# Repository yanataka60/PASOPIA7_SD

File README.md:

# TOSHIBA PASOPIA7、PASOPIAにSD-Cardとのロード、セーブ機能

　TOSHIBA PASOPIA7、PASOPIA(T-BASIC Ver1.1)でCMTの代わりにSD-CARDからロード、セーブを実現するものです。

　SDから読み込めるCMTのファイル形式はEMUで一般的なWAV、CASには対応していません。bugfire2009さんのDumpListEditorを使ってバイナリ形式に変換したものを使います。

　機械語 -> 各モデル固有ヘッダ付きBINファイル、拡張子は.bin

　BASIC -> BASファイル、拡張子は.bas

　CMTからの読み込み実行に数分掛かっていたゲームも数十秒で実行できます。

　ただし、CMT用プログラムのすべてがSD対応となるわけではありません。特に市販ゲームはCMT読み込みに独自ルーチンを使っているものもあるため、SD対応は不明です。

　なお、Arduino、ROMへ書き込むための機器が別途必要となります。

#### 　PASOPIAは、T-BASIC Ver1.1のみの対応です。また、OA-BASICも未対応です。

## 重要!!
　PASOPIA、PASOPIA7においてあるあるの電源ユニット部フィルムコンデンサの破裂ですが、修理に適切な品への交換されていない場合、電源電圧は正常(+5V)なのに信号電圧が異常(+10V程度)な状態となることがあるようです。

　私は当初電源電圧が正常であることを確認したものの原因が判らずArduino及びUSBシリアル変換モジュールを数個破壊してしまいました。

　当方ではCZRD信号の電圧が異常だったため、念のためPASOPIA7_SD基板にCZRD信号電圧を測るための「J6 TEST_VOL」端子を設けてあります。

　ICを装着する前に電圧をチェックし、+5V以上の電圧が出ているようであればまず電源ユニット部フィルムコンデンサを適切な品に交換してください。

　また、事前に調査するのであればPAC SLOT2 15Pin(CRD)の電圧を測ってみてください。

## 回路図(PASOPIA7、PASOPIA共通)
　PASOPIA7_SD本体基板とPASOPIA7_SD_ROM基板に分かれています。

　SDアクセスルーチンを読み込むためにPASOPIA7_SD_ROM基板(読込専用RAMPAC)を使用します。

　XPAC2又はRAMPACを持っていればそれにCMTから読み込んだSDアクセスルーチンを保存しておくことで使用することも可能です。詳細は後述の「XPAC2又はRAMPACの使用」を参照してください。

### PASOPIA7_SD本体基板
　KiCadフォルダ内のPASOPIA7_SD.PDFを参照してください。

[回路図](https://github.com/yanataka60/PASOPIA7_SD/blob/main/Kicad/1.6/PASOPIA7_SD.pdf)

## 部品
|番号|品名|数量|備考|
| ------------ | ------------ | ------------ | ------------ |
|J1|2x25ボックスヘッダ|1|共立エレショップ JS-1200R-50など、秋月電子通商 PH-2x40RGなどのピンヘッダでも代用可(注4)|
||J2,J3のいずれか|||
|J2|Micro_SD_Card_Kit|1|秋月電子通商 AE-microSD-LLCNV (注1)|
|J3|MicroSD Card Adapter|1|Arduino等に使われる5V電源に対応したもの(注2)|
|U1|74LS04|1||
|U2|74LS30|1||
|U3|8255|1||
|U4|Arduino_Pro_Mini_5V|1|Atmega328版を使用 168版は不可。(注3)|
|C1-C3|積層セラミックコンデンサ 0.1uF|3||
|C4|電解コンデンサ 16v100uF|1||
|S1|3Pスライドスイッチ|1|秋月電子通商 SS12D01G4など|
|J4|コネクタ 2Pin|1|ピンヘッダで代用するときはGNDと間違えないよう1Pinで5Vだけにしたほうが良い|
|J5|DCジャック|1|秋月電子通商 MJ-179PHなど|
|J6|2P ピンヘッダ|1|秋月電子通商 PH-1x40SGなど|
||2.54mmピッチ2x25Pinフラットケーブル|1||
||PASOPIA7_SDとPASOPIA7_SD_ROMを繋ぐケーブル|15cm～30cm|ジャンプワイヤー メス-メスなど|

PASOPIA7_SDに外部から電源を供給する場合
|番号|品名|数量|備考|
| ------------ | ------------ | ------------ | ------------ |
||ACアダプター 5V|1|秋月電子通商 M050200-A010JPなど|

### 注1)秋月電子通商　AE-microSD-LLCNVのJ1ジャンパはショートしてください。

### 注2)MicroSD Card Adapterを使う場合

J3に取り付けます。

MicroSD Card Adapterについているピンヘッダを除去してハンダ付けするのが一番確実ですが、J2の穴にMicroSD Card Adapterをぴったりと押しつけ、裏から多めにハンダを流し込むことでハンダ付けをする方法もあります。なお、この方法の時にはしっかりハンダ付けが出来たかテスターで導通を確認しておいた方が安心です。

ハンダ付けに自信のない方はJ1の秋月電子通商　AE-microSD-LLCNVをお使いください。AE-microSD-LLCNVならパワーLED、アクセスLEDが付いています。

### 注3)Arduino Pro MiniはA4、A5ピンも使っています。

#### 注4)ピンヘッダで代用するときは、基板から若干浮かせてピンヘッダをハンダ付けするとフラットケーブルをスムーズに抜き差しできます。

### PASOPIA7_SD_ROM基板
　KiCadフォルダ内のPASOPIA7_SD.PDFを参照してください。

[回路図](https://github.com/yanataka60/PASOPIA7_SD/blob/main/Kicad/ROM/PASOPIA7_SD_ROM.pdf)

|番号|品名|数量|備考|
| ------------ | ------------ | ------------ | ------------ |
|U1|74LS04|1||
|U2|74LS00|1||
|U3|74LS20|1||
|U4-U5|74LS273|2||
|U6|ROM 27256/29C256又は27512/27C512相当品|1|入手しやすいものでOK、28C256は不可|
|U7|74LS245|1||
|C1-C7|積層セラミックコンデンサ 0.1uF|7||
|C8|電解コンデンサ 16v100uF|1||
|S1|3Pin ピンヘッダーとジャンパーピン又は3Pスライドスイッチ|1|秋月電子通商 SS12D01G4など|
|J2|コネクタ 2Pin|1|ピンヘッダで代用するときはGNDと間違えないよう1Pinで5Vだけにしたほうが良い|

## 取り付け(PASOPIA7、PASOPIA共通)
　PASOPIA7_SD本体基板はPASOPIA7(PASOPIA)本体後部の拡張端子とフラットケーブルで接続します。50Pinフラットケーブルは、コネクタのボッチとケーブルの返しが両方上になる側のコネクタを本体に嵌めます。

　ケーブルの返しを下にして本体に嵌めると一見嵌っているように見えても接触不良を起こしていることがあります。

.JPG)

　PASOPIA7_SD_ROM基板はPACスロット2に挿入します。この時PASOPIA7_SD_ROM基板は部品実装面を手前にして挿入してください。基板の右端をスロットの右に合わせるように挿入すればズレずに挿入できると思います。

　次にPASOPIA7_SD_ROM基板への+5V供給のため、PASOPIA7_SD_ROM基板の+5V端子(J2)とPASOPIA7_SD本体基板の+5V端子(J4)を繋いでください。

.JPG)

　XPAC2又はRAMPACを使用するときは、外部電源として5V電源アダプタを接続するか、内部電源としてPAC SLOT1の43Pin又は44Pinから+5Vを取り出してジャンプワイヤー オス-メスなどで接続します。

## ROMへの書込み(PASOPIA7、PASOPIA共通)
　Z80フォルダ内のRAMPAC.binをROMライター(TL866II Plus等)を使って27256又は27512に書き込みます。

　実際に使用しているのは32KByte分(32Kx8)です。

　PASOPIA7_SD_ROM基板のROMはPASOPIA7(PASOPIA)からはRAMPACとして扱われます。(PASOPIA7(PASOPIA)から書き込みはできません。)

## RAMPAC.binに登録されているファイル
　RAMPAC.binに登録されているファイルは次の2つになります。

|ファイル名|種類|備考|
| ------------ | ------------ | ------------ |
|sd|BASIC|PASOPIA7用|
|SDBOOT|BINARY|PASOPIA7用|
|sdt|BASIC|PASOPIA用|
|SDTBOOT|BINARY|PASOPIA用|

　また、RAMPAC.binへのファイル登録はTAKEDAさんのEMU ePASOPIA7で行っており、RAMPAC1としてファイルを選択すればePASOPIA7から読み書き出来ます。

## XPAC2又はRAMPACの使用(PASOPIA7、PASOPIA共通)
　XPAC2又はRAMPACを持っていればPASOPIA7_SD_ROM基板の代わりに使用できます。

　ただし、PASOPIA7_SD本体基板への+5V供給を独自に用意する必要があります。内部から引き出すか、5V電源アダプタを用意するかですが、PACスロット1 44Pinから取るのが簡単だと思います。

### XPAC2
　ePASOPIA7で扱うRAMPACKが32KByteなのに対してXPAC2で扱うSLOT4は64KByteです。

　XPAC2のSD-CARDへRAMPAC.binをコピーしてXPAC2 SLOT4へ登録することも可能とは思われますが、容量が32KByteとなってしまう気がします。

　XPAC2 SLOT4を64KByteのまま使いたいのであればsd.wav(sdt.wav)、SDBOOT.wav(SDTBOOT.wav)をCMTインタフェースから読み込み、XPAC2 SLOT4へ保存してください。

### RAMPAC
　RAMPAC.binをRAMPACへ登録する方法がありませんのでsd.wav(sdt.wav)、SDBOOT.wav(SDTBOOT.wav)をCMTインタフェースから読み込み、RAMPACへ保存してください。

## Arduinoプログラム(PASOPIA7、PASOPIA共通)
　Arduino IDEを使ってArduinoフォルダのPASOPIA7_SDフォルダ内PASOPIA7_SD.inoを書き込みます。

　SdFatライブラリを使用しているのでArduino IDEメニューのライブラリの管理からライブラリマネージャを立ち上げて「SdFat」をインストールしてください。

　「SdFat」で検索すれば見つかります。「SdFat」と「SdFat - Adafruit Fork」が見つかりますが「SdFat」のほうを使っています。

注)Arduinoを基板に直付けしている場合、Arduinoプログラムを書き込むときは、PASOPIA7(PASOPIA)本体とは接続を外し、U1 74LS04を外したうえで書き込んでください。

## SD-CARD(PASOPIA7、PASOPIA共通)
　出来れば8GB以下のSDカードを用意してください。

　ArduinoのSdFatライブラリは、SD規格(最大2GB)、SDHC規格(2GB～32GB)に対応していますが、SDXC規格(32GB～2TB)には対応していません。

　また、SDHC規格のSDカードであっても32GB、16GBは相性により動作しないものがあるようです。

　FAT16又はFAT32が認識できます。NTFSは認識できません。

## 操作方法
### PASOPIA7
　起動直後に「RUN"sd"」を実行してSDアクセスルーチンの読込、初期化の実行を行います。

　SDアクセスルーチンはE800h～EFCFhに読み込まれます。

　SDアクセスメニューを表示するにはA=&HE800:CALL Aを実行しますが、PF6ファンクションキーに登録してありますのでPF6ファンクションキーを押しても大丈夫です。

### PASOPIA(T-BASIC Ver1.1のみ対応)
　起動直後に「RUN"sdt"」を実行してSDアクセスルーチンの読込、初期化の実行を行います。

　SDアクセスルーチンはF000h～F776hに読み込まれます。

　SDアクセスメニューを表示するにはA=&HF000:CALL Aを実行しますが、PF6ファンクションキーに登録してありますのでPF6ファンクションキーを押しても大丈夫です。

#### 扱えるファイル(PASOPIA7、PASOPIA共通)
bugfire2009さんのDumpListEditorを使ってバイナリ形式に変換したものを使います。

扱う機種をPASOPIA7に変更したうえで変換します。

##### 機械語 -> 「BINファイル書出し(各モデル固有ヘッダ付き)」で保存、拡張子は.bin

##### BASIC -> 「BASファイル書出し」で保存、拡張子は.bas

### コマンド(PASOPIA7、PASOPIA共通)
　コマンド入力時にBSキー又は左カーソルキーで直前に入力した文字を訂正できます。

　CLR、HOME、上・下・右カーソルキーは画面が乱れるだけで入力文字の訂正は出来ません。

#### SD[RETURN]又はSD 文字列[RETURN]
　文字列を入力せずにSD[RETURN]のみ入力するとSD-CARDルートディレクトリにあるファイルの一覧を表示します。

　文字列を付けて入力すればSD-CARDルートディレクトリにあるその文字列から始まるファイルの一覧を表示します。
　10件表示したところで指示待ちになるのでESCキーで終了、Bキー又はBSキーで前の10件に戻ります。それ以外のキーで次の10件を表示します。

　表示される順番は、登録順となりファイル名アルファベッド順などのソートした順で表示することはできません。

　LOADしたいファイルを見つけたら左端の数字のキーを押せばLOADされます。

　BASICプログラムか、機械語プログラムかは自動で判断します。

　なお、PASOPIA7はE7FFh以降、PASOPIAはEFFFH以降へ機械語プログラムがLOADされた場合、次の五段階の挙動となります。

||PASOPIA7|PASOPIA|挙動|
|---- | ------------ | ------------ | ------------ |
|1|～E8FCh|～F0FAh|機械語プログラムをLOAD後は、SM,SBコマンドが使用できなくなります。LM,LG,LB,SD,J,Q,Bコマンドは使用できます。|
|2|～EC54h|～F423h|機械語プログラムをLOAD後は、J,Q,Bのみ使えます。SD,LMコマンドでLOADした後、Jコマンドでの実行は可能です。|
|3|～EDC6h|～F582h|BASICプログラムLOADの限界です。通常はCLEAR文で設定したメインメモリの上限E800hですが、F000hに変更すればEDC6hまでのBASICプログラムを一度だけLOAD出来ます。|
|4|～EE61h|～F614h|BASIC中からはこれ以降への機械語LOADは出来ません。|
|5|～EEE7h|～F691h|機械語プログラムをLOAD後は、すべてのコマンドが使えません。EDC7h以降までLOADされた場合は強制的に実行番地にジャンプを試みます。|

##### 例)
　　SD[RETURN]

　　SD S[RETURN]

　　SD SP[RETURN]

#### LM DOSファイル名[RETURN]
　指定したDOSフィル名の機械語プログラムをSD-CARDからLOADします。

　拡張子が「bin」であるファイルだけが対象でファイル名の最後が「.BIN」でない場合には自動的に付加されます。

　なお、PASOPIA7はE7FFh以降、PASOPIAはEFFFH以降へ機械語プログラムがLOADされた場合、次の五段階の挙動となります。

||PASOPIA7|PASOPIA|挙動|
|---- | ------------ | ------------ | ------------ |
|1|～E8FCh|～F0FAh|機械語プログラムをLOAD後は、SM,SBコマンドが使用できなくなります。LM,LG,LB,SD,J,Q,Bコマンドは使用できます。|
|2|～EC54h|～F423h|機械語プログラムをLOAD後は、J,Q,Bのみ使えます。SD,LMコマンドでLOADした後、Jコマンドでの実行は可能です。|
|3|～EDC6h|～F582h|BASICプログラムLOADの限界です。通常はCLEAR文で設定したメインメモリの上限E800hですが、F000hに変更すればEDC6hまでのBASICプログラムを一度だけLOAD出来ます。|
|4|～EE61h|～F614h|BASIC中からはこれ以降への機械語LOADは出来ません。|
|5|～EEE7h|～F691h|機械語プログラムをLOAD後は、すべてのコマンドが使えません。EDC7h以降までLOADされた場合は強制的に実行番地にジャンプを試みます。|

##### 例)
　　LM TEST[RETURN] -> DOSファイル名「TEST.BIN」を読み込みます。

　　LM TEST.BIN[RETURN] -> DOSファイル名「TEST.BIN」を読み込みます。

　　LM TEST.BAS[RETURN] -> DOSファイル名「TEST.BAS.BIN」を読み込みます。

#### LG DOSファイル名[RETURN]
　指定したDOSフィル名の機械語プログラムをSD-CARDからLOADした後、実行開始アドレスへジャンプします。

　LOAD後そのまま実行するのでFF64hまでLOADしても大丈夫です。

　LOADした後、実行開始アドレスへジャンプする以外はLMコマンドと同じです。

#### LB DOSファイル名[RETURN]
　現在選択しているPROGエリアに指定したDOSフィル名のBASICプログラムをSD-CARDからLOADします。

　LOADするPROGエリアを切り替えたい場合にはSDメニューに入る前に切り替えておいてください。

　拡張子が「BAS」であるファイルだけが対象でファイル名の最後が「.BAS」でない場合には自動的に付加されます。

##### 例)
　　LB TEST[RETURN] -> DOSファイル名「TEST.BAS」を読み込みます。

　　LB TEST.BAS[RETURN] -> DOSファイル名「TEST.BAS」を読み込みます。

　　LB TEST.BIN[RETURN] -> DOSファイル名「TEST.BIN.BAS」を読み込みます。

#### SM XXXX,YYYY,DOSファイル名[RETURN]　(XXXX,YYYYは16進数4桁を表す文字列)
　XXXX番地からYYYY番地までの機械語プログラムを指定したDOSフィル名でSD-CARDにSAVEします。

　拡張子の指定「.BIN」は省略することが出来、ファイル名の最後が「.BIN」でない場合には自動的に付加されます。

##### 例)
　　SM B000,BFFF,TEST[RETURN] -> B000h～BFFFhまでをDOSファイル名「TEST.BIN」でSAVEします。

　　SM B000,BFFF,TEST.BIN[RETURN] -> B000h～BFFFhまでをDOSファイル名「TEST.BIN」でSAVEします。

　　SM B000,BFFF,TEST.BAS[RETURN] -> B000h～BFFFhまでをDOSファイル名「TEST.BAS.BIN」でSAVEします。

#### SB DOSファイル名[RETURN]
　現在選択しているPROGエリアのBASICプログラムを指定したDOSフィル名でSD-CARDにSAVEします。

　SAVEするPROGエリアを切り替えたい場合にはSDメニューに入る前に切り替えておいてください。

　拡張子の指定「.BAS」は省略することが出来、ファイル名の最後が「.BAS」でない場合には自動的に付加されます。

##### 例)
　　SB TEST[RETURN] -> DOSファイル名「TEST.BAS」でSAVEします。

　　SB TEST.BAS[RETURN] -> DOSファイル名「TEST.BAS」でSAVEします。

　　SB TEST.BIN[RETURN] -> DOSファイル名「TEST.BIN.BAS」でSAVEします。

#### J[RETURN]又はJ 16進数4桁[RETURN]
　Jだけの場合は、直前にLOADした機械語プログラムの先頭番地へジャンプします。

　16進数4桁を指定した場合は16進数4桁が表すアドレスにジャンプします。

　Jの後ろに空白があっても無くても構いません。

#### B[RETURN]又はQ[RETURN]
　BASICに復帰します。

### BASICプログラム中から機械語プログラムをLOADする
#### PASOPIA7
　BASICプログラム中に「CALL &HE803:REM ファイル名」と記述することで機械語プログラムをLOAD出来ます。

　ファイル名はSDカードに保存されている拡張子も含めたファイル名を記述します。

　通常LOAD可能なのはCLEAR文で設定したメインメモリの上限E7FFhですが、F000hに変更すればEE61hまでのBASICプログラムをLOAD出来ます。

##### 例)

20 B=&HE803:CALL B:REM antiair.bin

#### PASOPIA(T-BASIC Ver1.1)
　BASICプログラム中に「CALL &HF003:REM ファイル名」と記述することで機械語プログラムをLOAD出来ます。

　ファイル名はSDカードに保存されている拡張子も含めたファイル名を記述します。

　通常LOAD可能なのはCLEAR文で設定したメインメモリの上限EFFFhですが、F7FChに変更すればF614hまでのBASICプログラムをLOAD出来ます。

##### 例)

20 B=&HE803:CALL B:REM antiair.bin

## 未解決事項(2025.8.11)
　PASOPIA7_SDからPASOPIA、PASOPIA7の両機種でいぬふと様のゲームを起動したとき、以下の症状が出ることがあります。

#### 　原因を調査中ですが特定に至っていません。しかし、CMTからの起動においては症状はでませんのでいぬふと様のゲームに問題があるのではなく、PASOPIA7_SD側の問題と思われますのでこの件に関していぬふと様に問い合わせることはご遠慮くださるようお願いします。

### PASOPIA
　表示がずれます。ゲーム起動直前にwidth 40を実行すると回避できるようです。

　PASOPIA7_SD起動時にwidth 40:width 36としていますが、それでも表示がずれる場合にはゲーム起動直前にwidth 40を実行してから起動してみてください。

### PASOPIA7
　いくつかのゲームで何も押していないのに勝手にキー入力され続けてしまうことがあります。また症状が出るときと出ない時があり、原因の特定に至っていません。

　症状が出ない時には普通にゲームができます。今のところ、回避方法、対策が見つかっていません。

## 操作上の注意
　電源を入れたままSD-CARDの抜き差しをする場合又は「SD-CARD INITIALIZE ERROR」と表示されたときは、SD-CARDを挿入後、SD、LM、LBコマンド等でSD-CARDに3回ほどアクセスすれば復旧します。

　SD-CARDの抜き差しは電源を切った状態で行うほうがより確実です。

## 謝辞
　基板の作成に当たり以下のデータを使わせていただきました。ありがとうございました。

　Arduino Pro Mini

　　https://github.com/g200kg/kicad-lib-arduino

　AE-microSD-LLCNV

　　https://github.com/kuninet/PC-8001-SD-8kRAM

## 追記
2025.8.14 PASOPIAはT-BASIC Ver1.1のみ対応していることを追記。BASICプログラム中から機械語プログラムをLOADするときのファイル名には拡張子も含めることを追記。

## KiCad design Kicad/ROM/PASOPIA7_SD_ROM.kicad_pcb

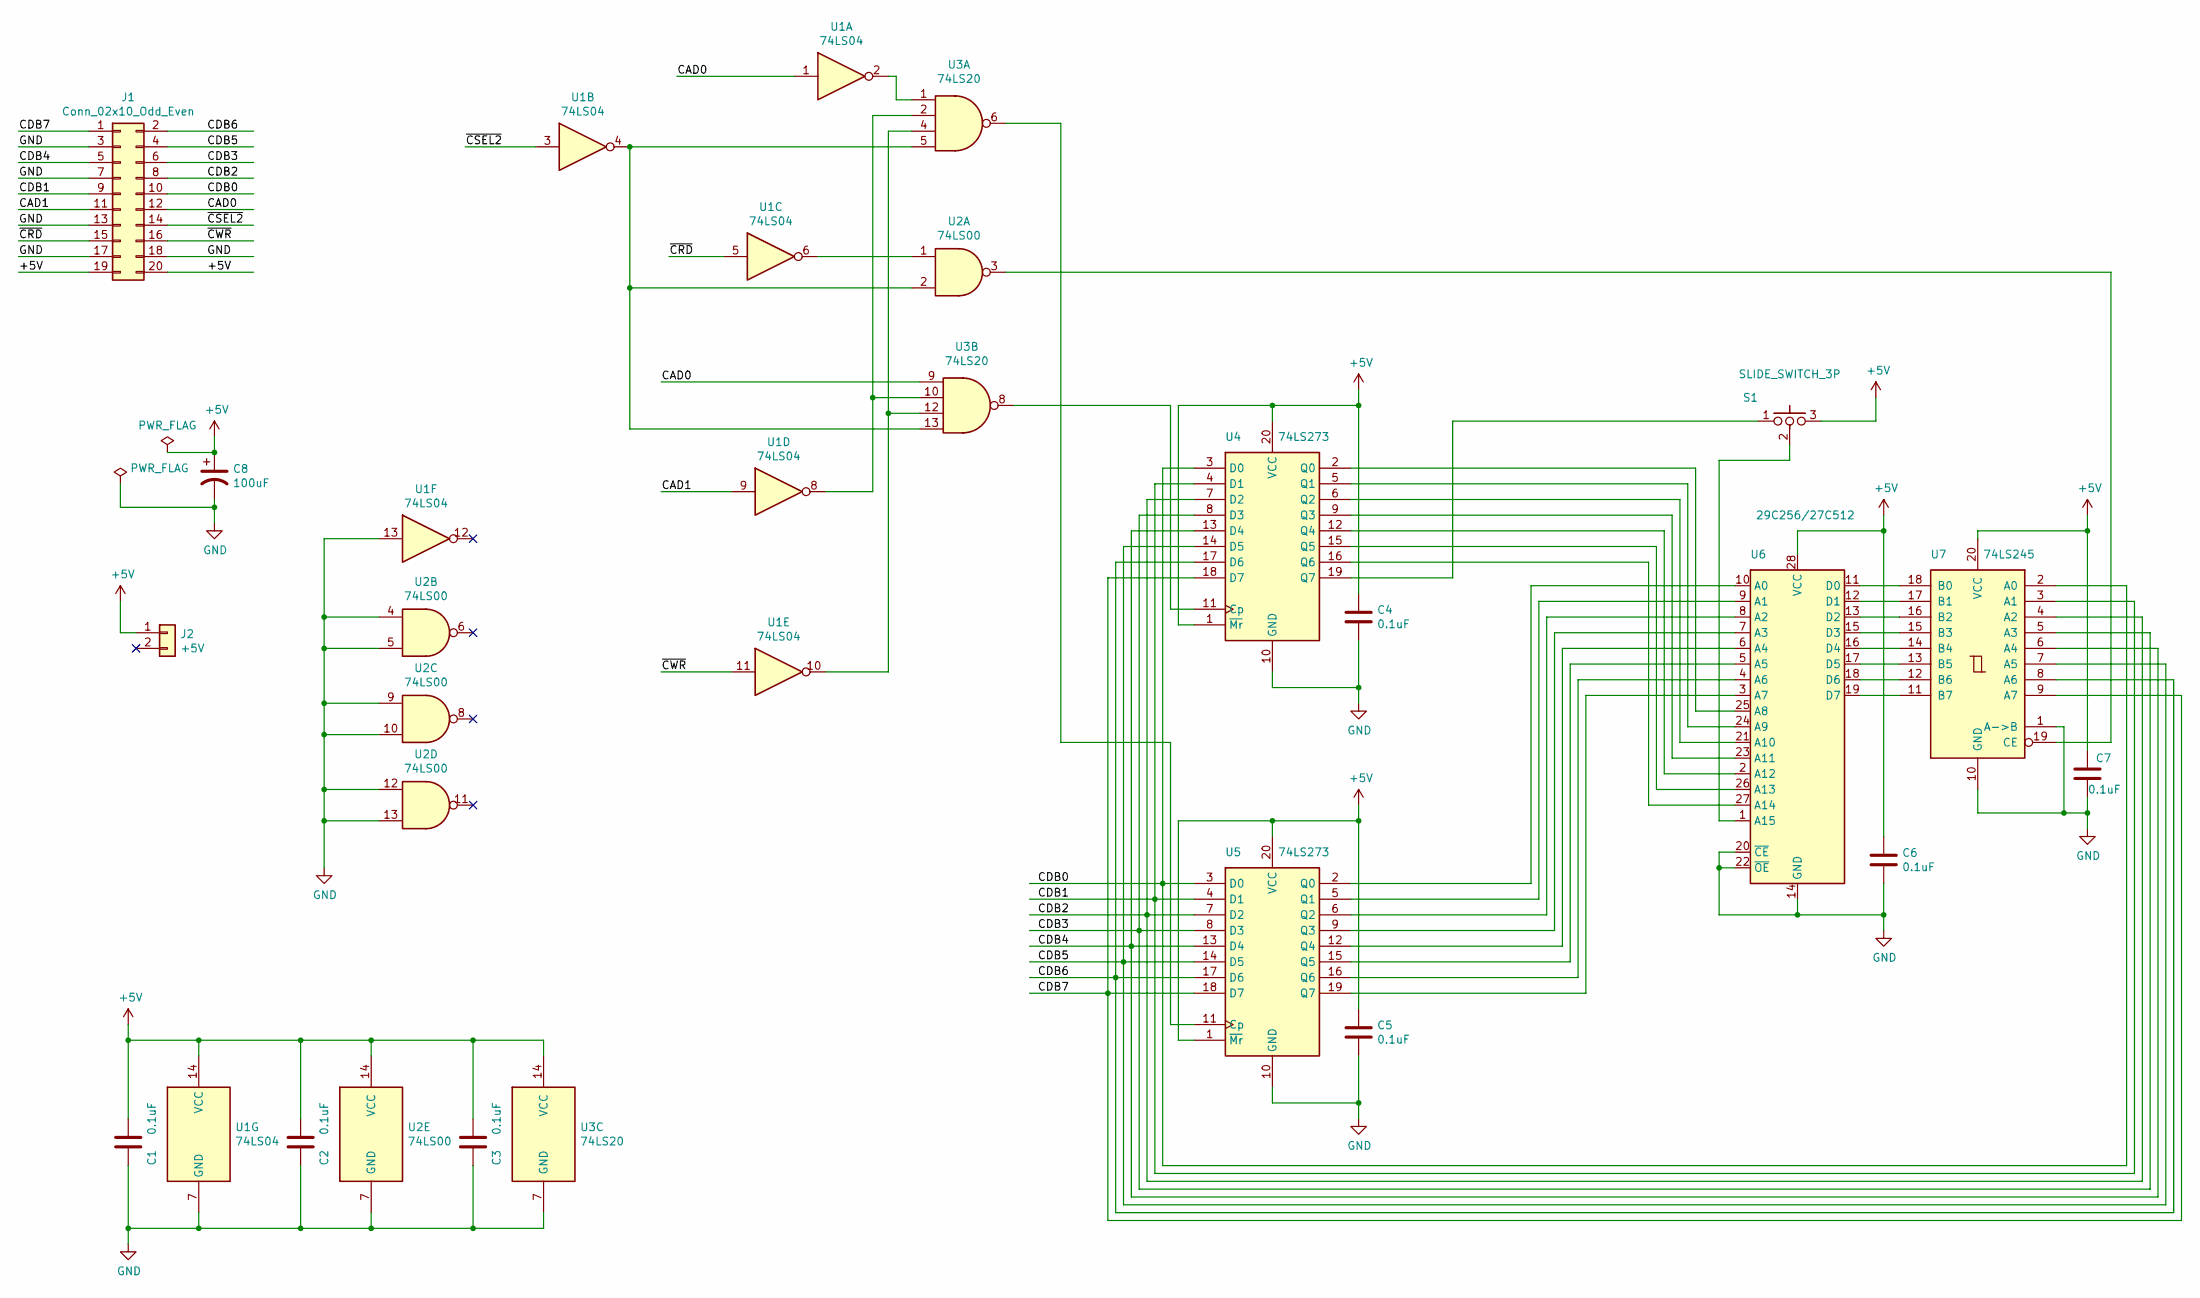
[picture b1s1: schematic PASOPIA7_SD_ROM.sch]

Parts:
C1, C2, C3, C4, C5, C6, C7: 0.1uF; C_Rect_L4.0mm_W2.5mm_P2.50mm
C8: 100uF; CP_Radial_D5.0mm_P2.50mm
J1: Conn_02x10_Odd_Even; PinHeader_2x10_P2.54mm_Vertical
J2: +5V; PinHeader_1x02_P2.54mm_Horizontal
S1: SLIDE_SWITCH_3P; PinHeader_1x03_P2.54mm_Vertical
U1: 74LS04; DIP-14_W7.62mm_LongPads
U2: 74LS00; DIP-14_W7.62mm_LongPads
U3: 74LS20; DIP-14_W7.62mm_LongPads
U4, U5: 74LS273; DIP-20_W7.62mm_LongPads
U6: 29C256/27C512; DIP-28_W15.24mm_LongPads
U7: 74LS245; DIP-20_W7.62mm_LongPads

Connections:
+5V: C1.2, C2.2, C3.2, C4.1, C5.1, C6.1, C7.1, C8.1, J1.19, J1.20, J2.1, S1.3, U1.14 (VCC), U2.14 (VCC), U3.14 (VCC), U4.1 (~Mr), U4.20 (VCC), U5.1 (~Mr), U5.20 (VCC), U6.28 (VCC), U7.20 (VCC)
/CAD0: J1.12, U1.1, U3.9
/CAD1: J1.11, U1.9
/CDB0: J1.10, U4.3 (D0), U5.3 (D0), U7.2 (A0)
/CDB1: J1.9, U4.4 (D1), U5.4 (D1), U7.3 (A1)
/CDB2: J1.8, U4.7 (D2), U5.7 (D2), U7.4 (A2)
/CDB3: J1.6, U4.8 (D3), U5.8 (D3), U7.5 (A3)
/CDB4: J1.5, U4.13 (D4), U5.13 (D4), U7.6 (A4)
/CDB5: J1.4, U4.14 (D5), U5.14 (D5), U7.7 (A5)
/CDB6: J1.2, U4.17 (D6), U5.17 (D6), U7.8 (A6)
/CDB7: J1.1, U4.18 (D7), U5.18 (D7), U7.9 (A7)
/~CRD: J1.15, U1.5
/~CSEL2: J1.14, U1.3
/~CWR: J1.16, U1.11
GND: C1.1, C2.1, C3.1, C4.2, C5.2, C6.2, C7.2, C8.2, J1.3, J1.7, J1.13, J1.17, J1.18, U1.7 (GND), U1.13, U2.4, U2.5, U2.7 (GND), U2.9, U2.10, U2.12, U2.13, U3.7 (GND), U4.10 (GND), U5.10 (GND), U6.14 (GND), U6.20 (~CE), U6.22 (~OE), U7.1 (A->B), U7.10 (GND)
unnamed: S1.1, U4.19 (Q7)
unnamed: S1.2, U6.1 (A15)
unnamed: U1.2, U3.1
unnamed: U1.4, U2.2, U3.5, U3.13
unnamed: U1.6, U2.1
unnamed: U1.8, U3.2, U3.10
unnamed: U1.10, U3.4, U3.12
unnamed: U2.3, U7.19 (CE)
unnamed: U3.6, U5.11 (Cp)
unnamed: U3.8, U4.11 (Cp)
unnamed: U4.2 (Q0), U6.25 (A8)
unnamed: U4.5 (Q1), U6.24 (A9)
unnamed: U4.6 (Q2), U6.21 (A10)
unnamed: U4.9 (Q3), U6.23 (A11)
unnamed: U4.12 (Q4), U6.2 (A12)
unnamed: U4.15 (Q5), U6.26 (A13)
unnamed: U4.16 (Q6), U6.27 (A14)
unnamed: U5.2 (Q0), U6.10 (A0)
unnamed: U5.5 (Q1), U6.9 (A1)
unnamed: U5.6 (Q2), U6.8 (A2)
unnamed: U5.9 (Q3), U6.7 (A3)
unnamed: U5.12 (Q4), U6.6 (A4)
unnamed: U5.15 (Q5), U6.5 (A5)
unnamed: U5.16 (Q6), U6.4 (A6)
unnamed: U5.19 (Q7), U6.3 (A7)
unnamed: U6.11 (D0), U7.18 (B0)
unnamed: U6.12 (D1), U7.17 (B1)
unnamed: U6.13 (D2), U7.16 (B2)
unnamed: U6.15 (D3), U7.15 (B3)
unnamed: U6.16 (D4), U7.14 (B4)
unnamed: U6.17 (D5), U7.13 (B5)
unnamed: U6.18 (D6), U7.12 (B6)
unnamed: U6.19 (D7), U7.11 (B7)

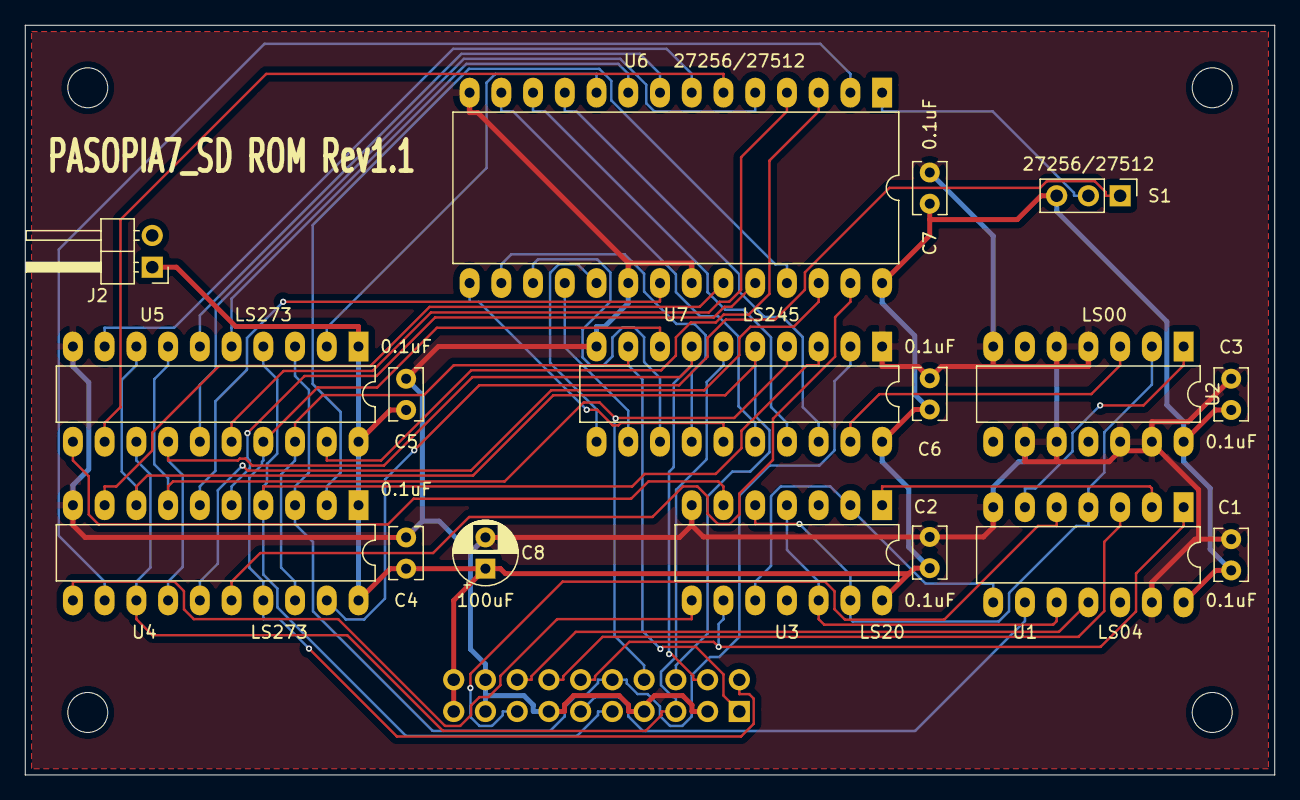
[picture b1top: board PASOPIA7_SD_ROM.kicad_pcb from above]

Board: 2 copper layers, 100.0 x 60.0 mm, 22 parts (1 on the bottom side), 48 nets.

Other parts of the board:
MH1, MH2, MH3, MH4: MountingHole_3.2mm_M3

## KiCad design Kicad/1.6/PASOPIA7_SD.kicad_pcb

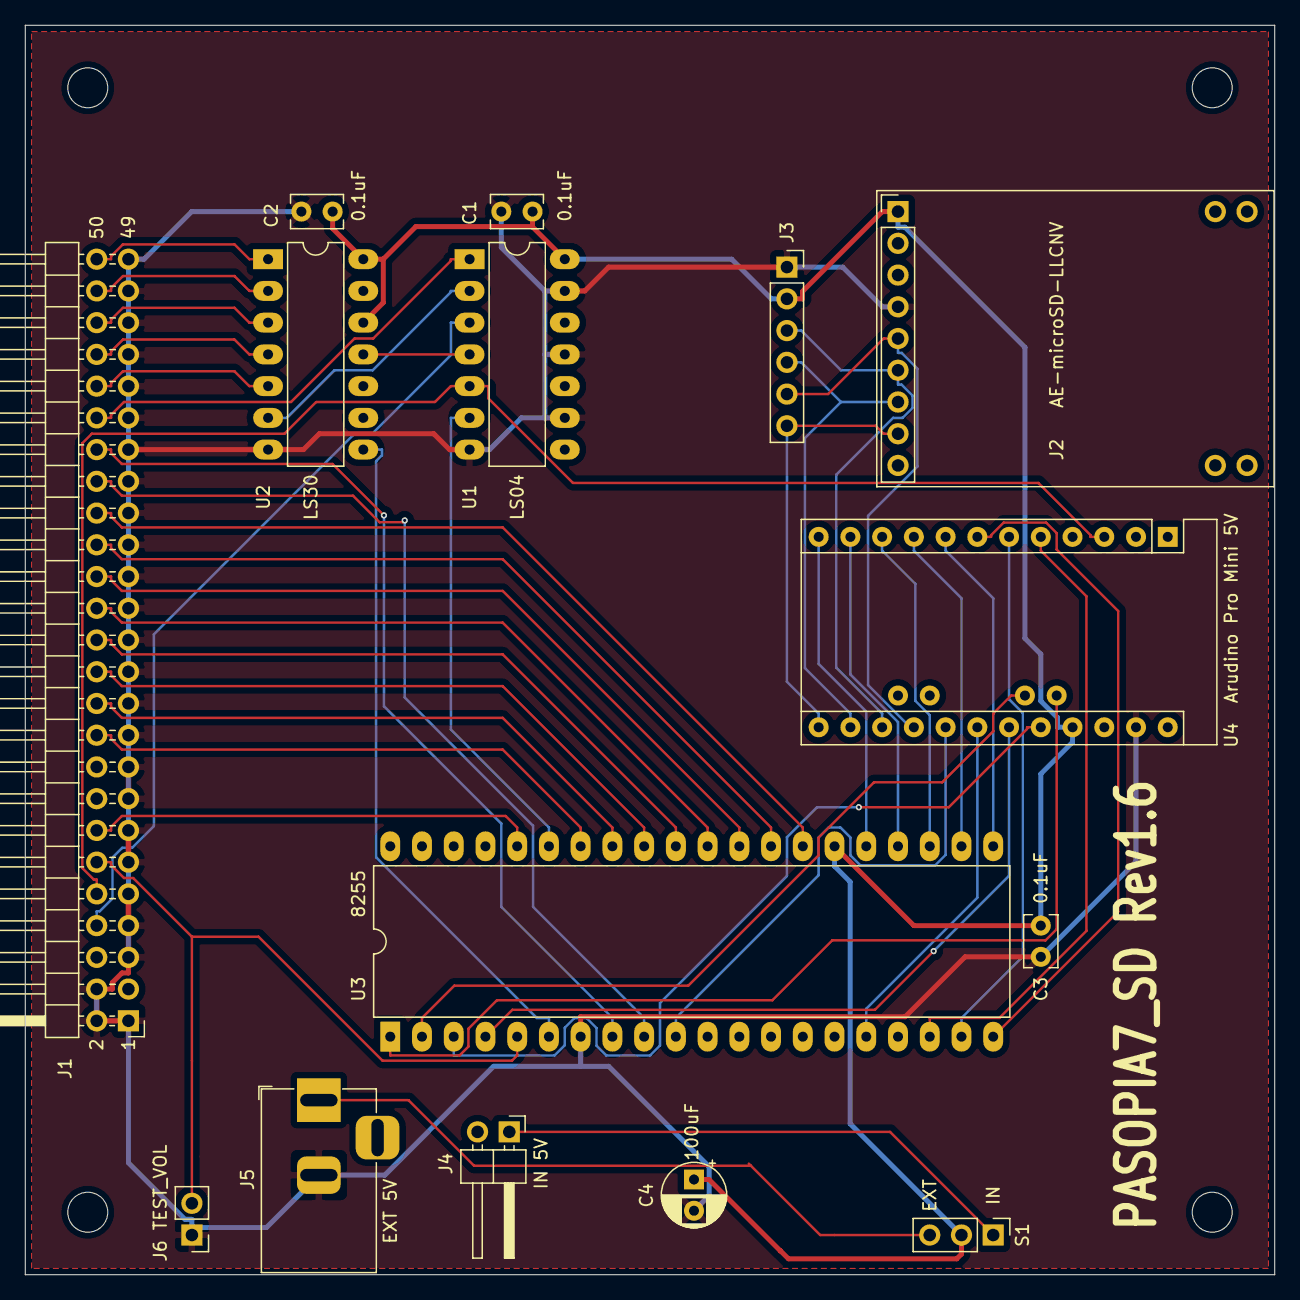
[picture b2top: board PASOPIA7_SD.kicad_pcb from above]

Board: 2 copper layers, 100.0 x 100.0 mm, 19 parts (0 on the bottom side), 46 nets.

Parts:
C1, C2, C3: 0.1uF; C_Rect_L4.0mm_W2.5mm_P2.50mm
C4: 100uF; CP_Radial_D5.0mm_P2.50mm
J1: PASOPIA7 BUS; PinHeader_2x25_P2.54mm_Horizontal
J2: Micro_SD_Card_Kit; AE-microSD-LLCNV
J3: MicroSD Card Adapter; PinSocket_1x06_P2.54mm_Vertical
J4: IN 5V; PinHeader_1x02_P2.54mm_Horizontal
J5: EXT 5V; BarrelJack_Horizontal
J6: TEST_VOL; PinHeader_1x02_P2.54mm_Vertical
MH1, MH2, MH3, MH4: MountingHole_3.2mm_M3
S1: IN / OUT; PinHeader_1x03_P2.54mm_Vertical
U1: 74LS04; DIP-14_W7.62mm_LongPads
U2: 74LS30; DIP-14_W7.62mm_LongPads
U3: 8255; DIP-40_W15.24mm_LongPads
U4: Arduino_Pro_Mini_5V; Arduino_Pro_Mini

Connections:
+5V: C1.2, C2.2, C3.1, C4.1, J2.1, J3.2, S1.2, U1.14, U2.12, U2.14, U3.26, U4.21
/CS: J2.8, J3.6, U4.13
/CZAD0: J1.36, U3.9
/CZAD1: J1.38, U3.8
/CZAD2: J1.40, U1.1
/CZAD3: J1.42, U2.5
/CZAD4: J1.44, U2.4
/CZAD5: J1.46, U2.3
/CZAD6: J1.48, U2.2
/CZAD7: J1.50, U2.1
/CZDB0: J1.20, U3.34
/CZDB1: J1.22, U3.33
/CZDB2: J1.24, U3.32
/CZDB3: J1.26, U3.31
/CZDB4: J1.28, U3.30
/CZDB5: J1.30, U3.29
/CZDB6: J1.32, U3.28
/CZDB7: J1.34, U3.27
/CZIORQ: J1.8, U1.3
/CZRD: J1.12, J6.2, U3.5
/CZRST: J1.10, U1.5, U4.3
/CZWR: J1.14, U3.36
/MISO: J2.6, J3.3, U4.15
/MOSI: J2.7, J3.4, U4.14
/SCK: J2.5, J3.5, U4.16
GND: C1.1, C2.1, C3.2, C4.2, J1.1, J1.2, J1.4, J1.5, J1.7, J1.9, J1.11, J1.13, J1.15, J1.17, J1.19, J1.21, J1.23, J1.25, J1.27, J1.29, J1.31, J1.33, J1.35, J1.37, J1.39, J1.41, J1.43, J1.45, J1.47, J1.49, J2.4, J3.1, J5.2, J6.1, U1.7, U1.9, U1.11, U1.13, U2.7, U3.7, U4.23
unnamed: J4.1, S1.1
unnamed: J5.1, S1.3
unnamed: U1.2, U2.6
unnamed: U1.4, U2.11
unnamed: U1.6, U3.35
unnamed: U2.8, U3.6
unnamed: U3.1, U4.A5
unnamed: U3.2, U4.A4
unnamed: U3.3, U4.20
unnamed: U3.4, U4.19
unnamed: U3.10, U4.17
unnamed: U3.16, U4.18
unnamed: U3.18, U4.5
unnamed: U3.19, U4.6
unnamed: U3.20, U4.7
unnamed: U3.21, U4.8
unnamed: U3.22, U4.9
unnamed: U3.23, U4.10
unnamed: U3.24, U4.11
unnamed: U3.25, U4.12
